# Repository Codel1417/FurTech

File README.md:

# FurTech

These are the files for a fursuit I am planning on making. I wanted eye displays for more expression, but then realized I cant see through the displays, Stereo cameras and an AR headset will be used for vision. The cameras will be hidden in the eyebrows. The jetson nano will handle stereo correction and managing the various sensors and servos. Once I have the hardware needed I will begin working on software. Base features are vision and ears reacting to sound. Then eye tracking using the cameras and opencv.

## Goals

* Eye Displays
* Ears which react to motion and environment
* Moving mouth to my voice
* Headpat detection and reactions
* Active cooling fan
* Stereo forward cameras
* AR/VR display for vision
* Eye Tracking (Vision or internal camera)
* No spaghetti 

## Hardware Features

Sensors connect over I2C

### Power Supply

* USB PD in @8-20V
* 3 5V 5A Linear Regulators
* Current Monitoring over I2C

### Sensors

* I2C Multiplexor
* Temperature Sensor
* 9-Axis IMU
* 5 Touch Sensors
* Cooling fan for comfort

### Ear Breakout

* Servo power switch
* i2C PWM Driver
* Mic/ADC input

### Display Driver

* 2 Display Connections
* Single output connection

### Jetson Nano Breakout

* I2C In
* Display SPI in
* Power in

## Other Hardware

* Nvidia Jetson Nano
* Nreal Air
* Stereo Cameras 1080P@60
* Usb PD battery
* 2x MatrixOrbital EVE3/4 displays
* 6x SG90 Servos

## 3D Printer STLs

* [https://www.thingiverse.com/thing:717901](https://www.thingiverse.com/thing:717901)

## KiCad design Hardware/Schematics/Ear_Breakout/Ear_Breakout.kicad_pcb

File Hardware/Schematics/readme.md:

The schematics were designed in [KiCad](https://www.kicad.org/) and use a consistent Resistor/Capacitor/LED size of 0603/1608 for ease of hand soldering. The AutoRouter plugin was used for data and low current traces. JST connectors are used to connect each board together.

Why split the boards? I was concerned about limited space inside the head so smaller boards let me contour the shape of the fursuit to reduce cable lengths and reduce the need to upscale the head. Smaller boards also allows for cheaper at con component swap out if something breaks.

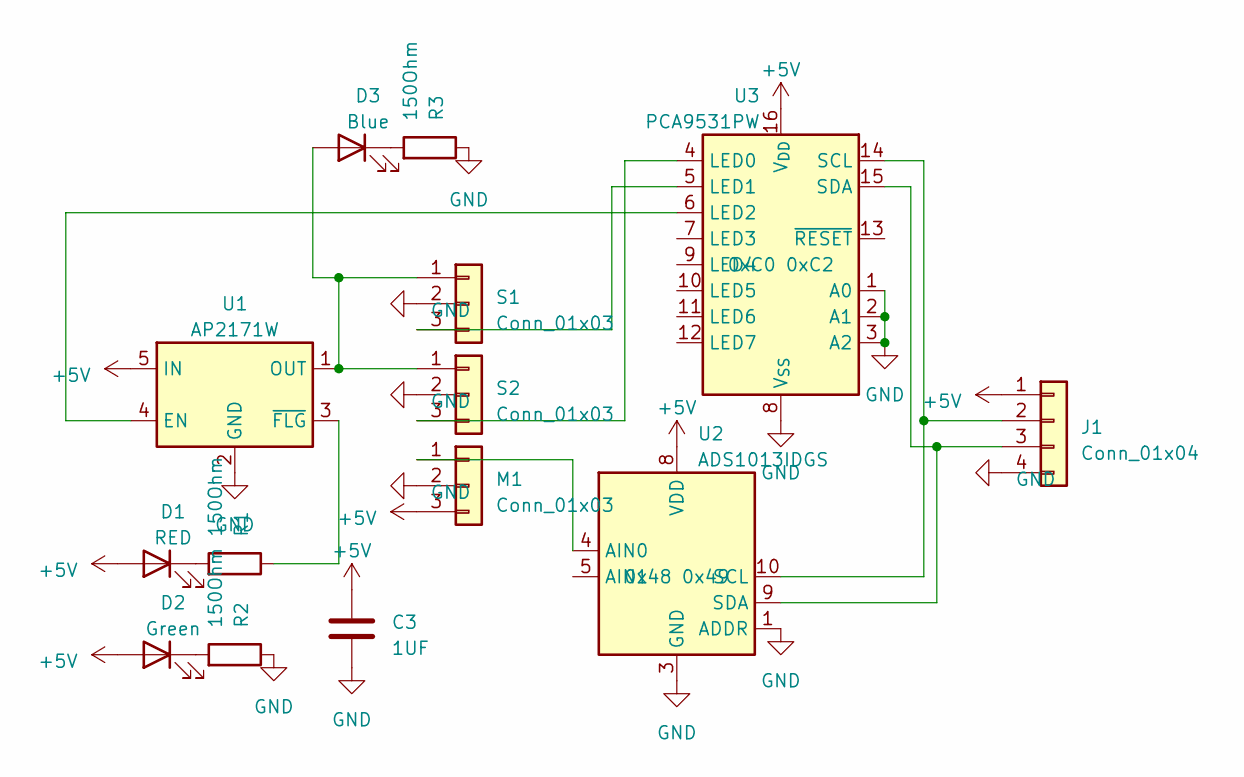
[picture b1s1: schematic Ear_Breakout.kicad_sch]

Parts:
C3: 1UF; C_0603_1608Metric_Pad1.08x0.95mm_HandSolder
D1: RED; LED_0603_1608Metric_Pad1.05x0.95mm_HandSolder
D2: Green; LED_0603_1608Metric_Pad1.05x0.95mm_HandSolder
D3: Blue; LED_0603_1608Metric_Pad1.05x0.95mm_HandSolder
J1: Conn_01x04; JST_EH_S4B-EH_1x04_P2.50mm_Horizontal
M1: Conn_01x03; PinHeader_1x03_P2.54mm_Horizontal
R1, R2, R3: 150Ohm; R_0603_1608Metric_Pad0.98x0.95mm_HandSolder
S1, S2: Conn_01x03; PinHeader_1x03_P2.54mm_Horizontal
U1: AP2171W; SOT-23-5
U2: ADS1013IDGS; TSSOP-10_3x3mm_P0.5mm
U3: PCA9531PW; TSSOP-16_4.4x5mm_P0.65mm

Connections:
+5V: C3.1, D1.2 (A), D2.2 (A), J1.1, M1.3, U1.5 (IN), U2.8 (VDD), U3.16 (V_{DD})
GND: C3.2, J1.4, M1.2, R2.1, R3.1, S1.2, S2.2, U1.2 (GND), U2.1 (ADDR), U2.3 (GND), U3.1 (A0), U3.2 (A1), U3.3 (A2), U3.8 (V_{SS})
unnamed: D1.1 (K), R1.2
unnamed: D2.1 (K), R2.2
unnamed: D3.2 (A), S1.1, S2.1, U1.1 (OUT)
unnamed: D3.1 (K), R3.2
unnamed: J1.2, U2.10 (SCL), U3.14 (SCL)
unnamed: J1.3, U2.9 (SDA), U3.15 (SDA)
unnamed: M1.1, U2.4 (AIN0)
unnamed: S1.3, U3.5 (LED1)
unnamed: S2.3, U3.4 (LED0)
unnamed: U1.4 (EN), U3.6 (LED2)
unnamed: R1.1, U1.3 (~FLG)

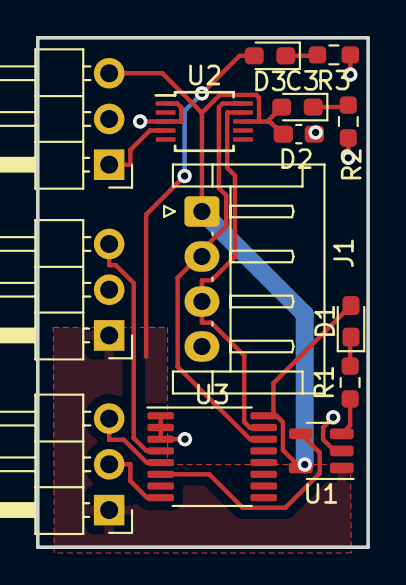
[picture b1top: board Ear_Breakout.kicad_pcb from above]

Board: 2 copper layers, 18.3 x 28.3 mm, 14 parts (0 on the bottom side), 13 nets.

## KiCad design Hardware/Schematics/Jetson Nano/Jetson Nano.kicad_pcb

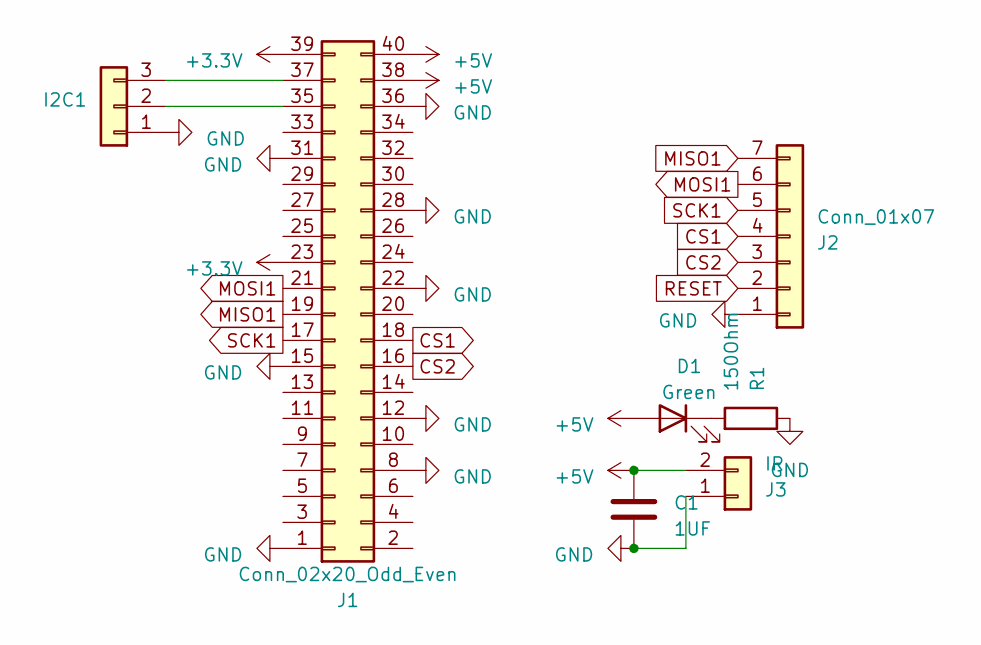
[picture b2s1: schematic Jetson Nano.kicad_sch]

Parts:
C1: 1UF; C_0603_1608Metric_Pad1.08x0.95mm_HandSolder
D1: Green; LED_0603_1608Metric_Pad1.05x0.95mm_HandSolder
I2C1: Conn_01x04; JST_EH_S3B-EH_1x03_P2.50mm_Horizontal
J1: Conn_02x20_Odd_Even; PinSocket_2x20_P2.54mm_Vertical
J2: Conn_01x07; JST_EH_S7B-EH_1x07_P2.50mm_Horizontal
J3: IR; JST_EH_S2B-EH_1x02_P2.50mm_Horizontal
R1: 150Ohm; R_0603_1608Metric_Pad0.98x0.95mm_HandSolder

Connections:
+3.3V: J1.23, J1.39
+5V: C1.1, D1.2 (A), J1.38, J1.40, J3.2
CS1: J1.18, J2.4
CS2: J1.16, J2.3
GND: C1.2, I2C1.1, J1.1, J1.8, J1.12, J1.15, J1.22, J1.28, J1.31, J1.36, J2.1, J3.1, R1.1
MISO1: J1.19, J2.7
MOSI1: J1.21, J2.6
unnamed: D1.1 (K), R1.2
unnamed: I2C1.2, J1.35
unnamed: I2C1.3, J1.37
RESET: J2.2
SCK1: J1.17, J2.5

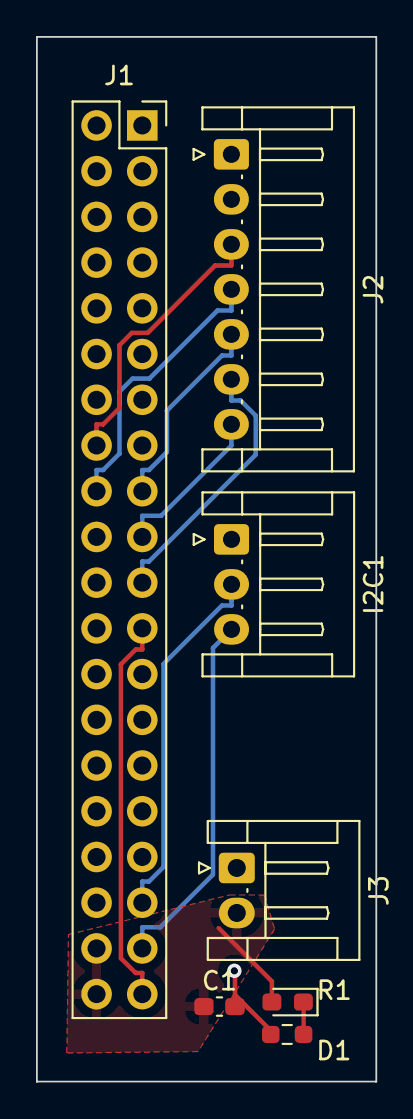
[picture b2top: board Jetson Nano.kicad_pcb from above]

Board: 2 copper layers, 18.9 x 58.0 mm, 7 parts (0 on the bottom side), 11 nets.

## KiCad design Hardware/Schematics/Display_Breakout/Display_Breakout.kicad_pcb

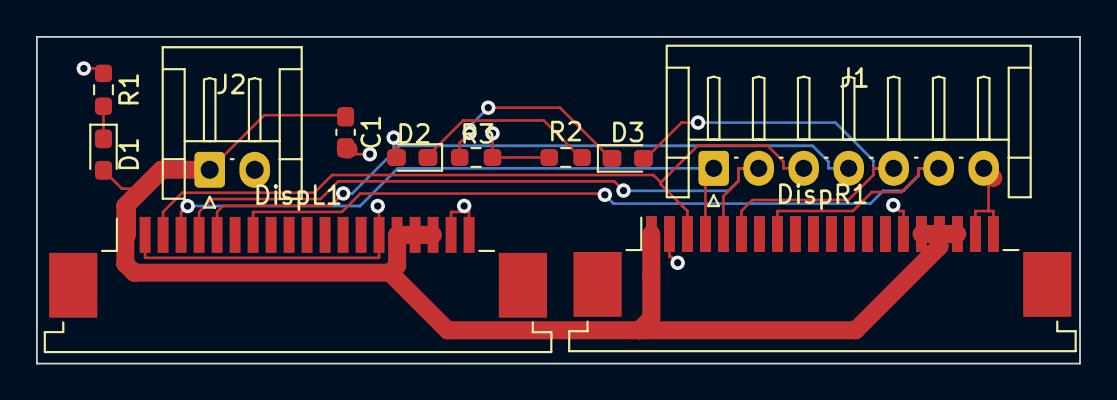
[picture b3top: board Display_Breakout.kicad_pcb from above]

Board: 2 copper layers, 57.9 x 18.1 mm, 11 parts (0 on the bottom side), 11 nets.

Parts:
C1: 4.7uf; C_0603_1608Metric_Pad1.08x0.95mm_HandSolder
D1: Green; LED_0603_1608Metric_Pad1.05x0.95mm_HandSolder
D2, D3: Blue; LED_0603_1608Metric_Pad1.05x0.95mm_HandSolder
DispL1: Conn_02x10_Odd_Even; TE_2-84952-0_1x20-1MP_P1.0mm_Horizontal
DispR1: Conn_02x10_Odd_Even; TE_2-84952-0_1x20-1MP_P1.0mm_Horizontal
J1: Conn_01x07; JST_EH_S7B-EH_1x07_P2.50mm_Horizontal
J2: Conn_01x02; JST_EH_S2B-EH_1x02_P2.50mm_Horizontal
R1, R2, R3: 150Ohm; R_0603_1608Metric_Pad0.98x0.95mm_HandSolder

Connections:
+5V: C1.1, D1.2 (A), DispL1.1, DispL1.16, DispL1.17, DispL1.18, DispR1.1, DispR1.16, DispR1.17, DispR1.18, J2.1
CS1: D2.2 (A), DispL1.6, J1.4
CS2: D3.2 (A), DispR1.6, J1.5
GND: C1.2, DispL1.2, DispL1.15, DispL1.19, DispL1.20, DispR1.2, DispR1.15, DispR1.19, DispR1.20, J1.7, J2.2, R1.1, R2.1, R3.1
MISO1: DispL1.4, DispR1.4, J1.1
MOSI1: DispL1.5, DispR1.5, J1.2
unnamed: D1.1 (K), R1.2
unnamed: D2.1 (K), R2.2
unnamed: D3.1 (K), R3.2
RESET: DispL1.8, DispR1.8, J1.6
SCK1: DispL1.3, DispR1.3, J1.3

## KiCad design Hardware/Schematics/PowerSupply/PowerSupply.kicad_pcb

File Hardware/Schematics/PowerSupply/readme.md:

The original design was for an external 18650 battery pack but due to safety concerns I switched to USB C and premade packs.

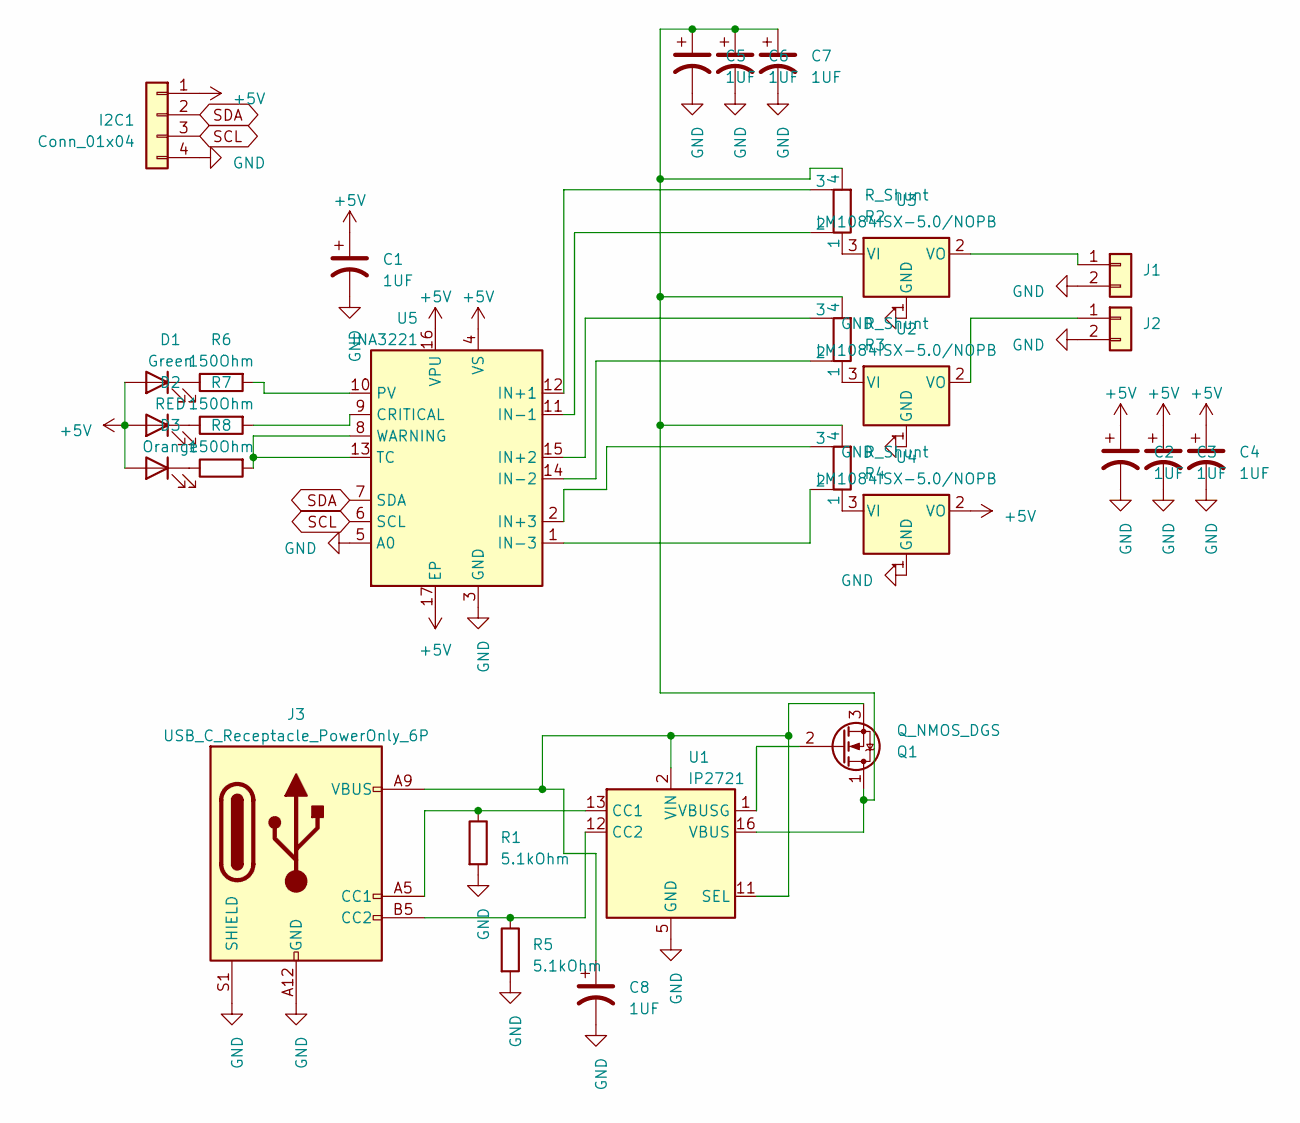
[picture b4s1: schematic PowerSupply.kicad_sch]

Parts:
C1, C2, C3, C4, C5, C6, C7, C8: 1UF; C_0603_1608Metric_Pad1.08x0.95mm_HandSolder
D1: Green; LED_0603_1608Metric_Pad1.05x0.95mm_HandSolder
D2: RED; LED_0603_1608Metric_Pad1.05x0.95mm_HandSolder
D3: Orange; LED_0603_1608Metric_Pad1.05x0.95mm_HandSolder
I2C1: Conn_01x04; JST_EH_S4B-EH_1x04_P2.50mm_Horizontal
J1, J2: JST_EH_S2B-EH_1x02_P2.50mm_Horizontal
J3: USB_C_Receptacle_PowerOnly_6P; USB_C_Receptacle_GCT_USB4135-GF-A_6P_TopMnt_Horizontal
Q1: Q_NMOS_DGS; TO-252-3_TabPin2
R1, R5: 5.1kOhm; R_0603_1608Metric
R2, R3, R4: R_Shunt; R_Shunt_Ohmite_LVK12
R6, R7, R8: 150Ohm; R_0603_1608Metric
U1: IP2721; TSSOP-16_4.4x5mm_P0.65mm
U2, U3, U4: LM1084ISX-5.0/NOPB; TO-263-3_TabPin2
U5: INA3221; Texas_RGV_S-PVQFN-N16_EP2.1x2.1mm

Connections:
+5V: C1.1, C2.1, C3.1, C4.1, D1.2 (A), D2.2 (A), D3.2 (A), I2C1.1, U4.2 (VO), U5.4 (VS), U5.16 (VPU), U5.17 (EP)
GND: C1.2, C2.2, C3.2, C4.2, C5.2, C6.2, C7.2, C8.2, I2C1.4, J1.2, J2.2, J3.A12 (GND), J3.B12 (GND), J3.S1 (SHIELD), R1.2, R5.2, U1.5 (GND), U2.1 (GND), U3.1 (GND), U4.1 (GND), U5.3 (GND), U5.5 (A0)
unnamed: D1.1 (K), R6.1
unnamed: D2.1 (K), R7.1
unnamed: D3.1 (K), R8.1
unnamed: J1.1, U3.2 (VO)
unnamed: J2.1, U2.2 (VO)
unnamed: J3.A5 (CC1), R1.1, U1.13 (CC1)
unnamed: J3.B5 (CC2), R5.1, U1.12 (CC2)
unnamed: C5.1, C6.1, C7.1, Q1.1 (D), R2.4, R3.4, R4.4, U1.16 (VBUS)
unnamed: Q1.2 (G), U1.1 (VBUSG)
unnamed: C8.1, J3.A9 (VBUS), J3.B9 (VBUS), Q1.3 (S), U1.2 (VIN), U1.11 (SEL)
unnamed: R3.1, U2.3 (VI)
unnamed: R2.1, U3.3 (VI)
unnamed: R4.1, U4.3 (VI)
unnamed: R7.2, U5.9 (CRITICAL)
unnamed: R2.3, U5.12 (IN+1)
unnamed: R3.3, U5.15 (IN+2)
unnamed: R4.3, U5.2 (IN+3)
unnamed: R2.2, U5.11 (IN-1)
unnamed: R3.2, U5.14 (IN-2)
unnamed: R4.2, U5.1 (IN-3)
unnamed: R6.2, U5.10 (PV)
unnamed: R8.2, U5.8 (WARNING), U5.13 (TC)
SCL: I2C1.3, U5.6 (SCL)
SDA: I2C1.2, U5.7 (SDA)

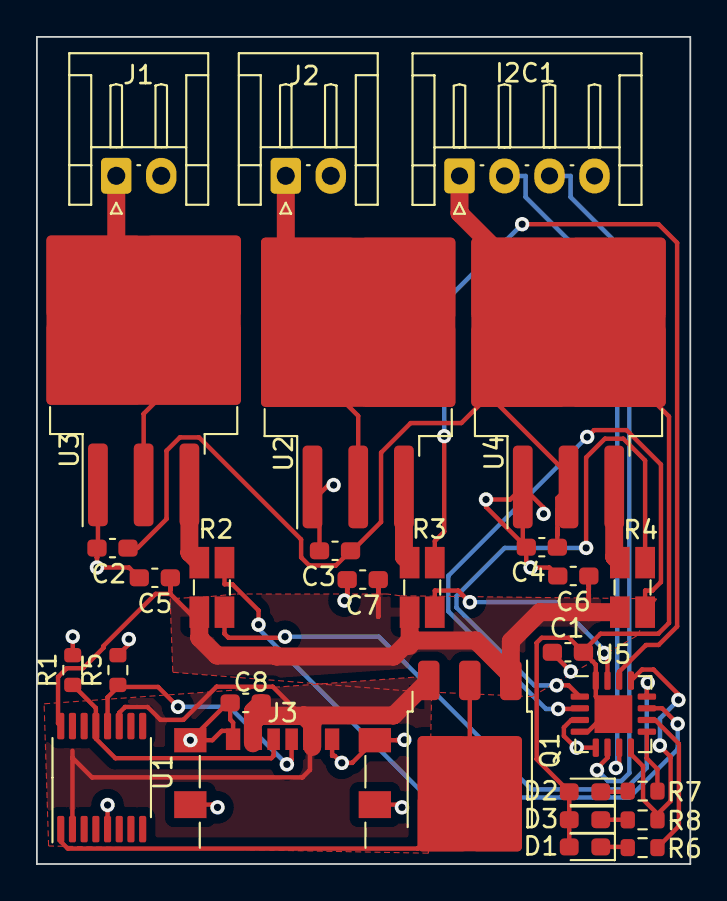
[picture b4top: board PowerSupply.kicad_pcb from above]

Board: 2 copper layers, 36.3 x 46.0 mm, 29 parts (0 on the bottom side), 26 nets.

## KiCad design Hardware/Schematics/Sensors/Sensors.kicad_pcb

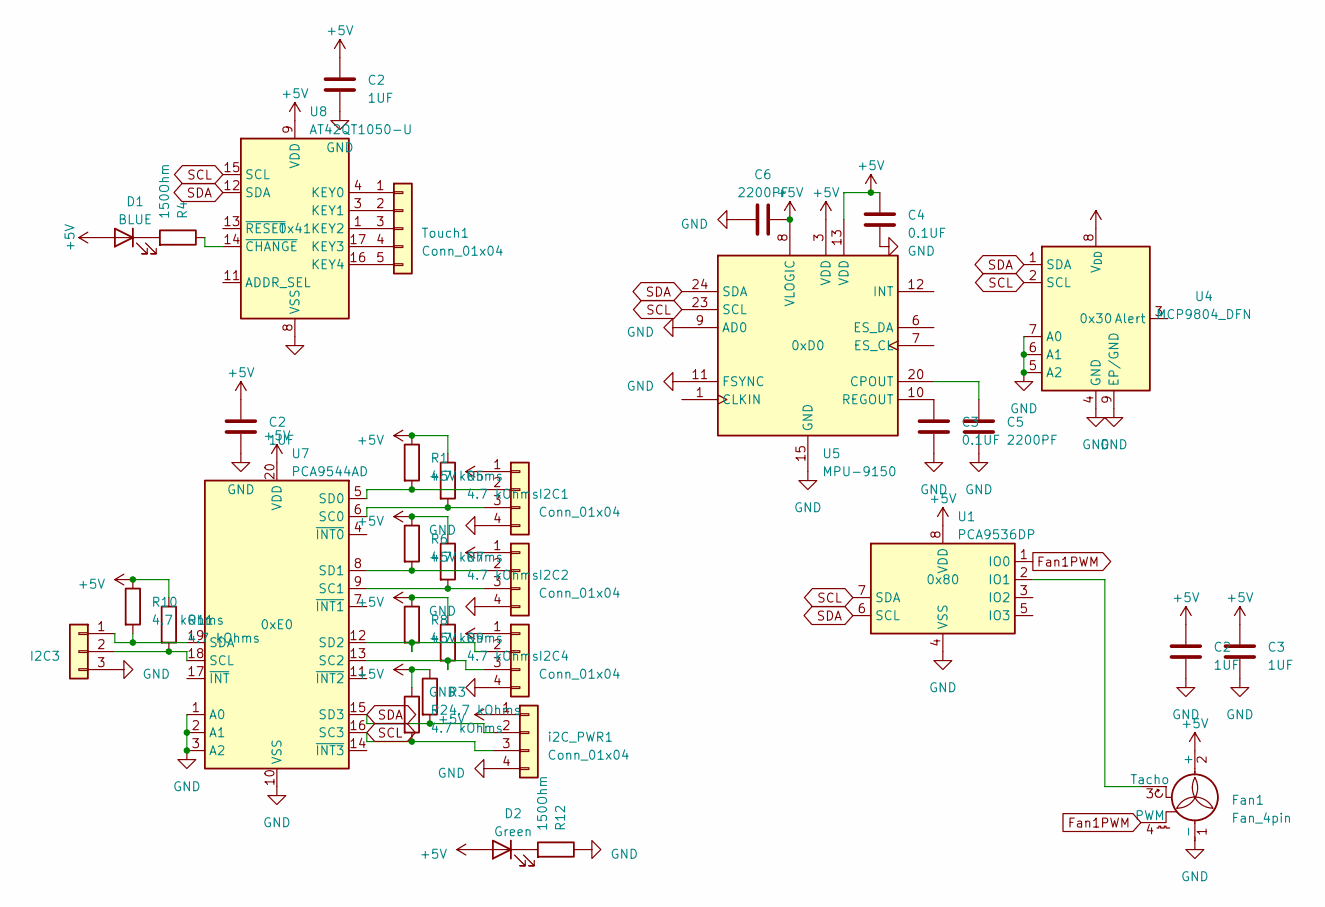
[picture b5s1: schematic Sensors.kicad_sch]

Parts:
C2: 1UF; C_0603_1608Metric_Pad1.08x0.95mm_HandSolder
C3, C4: 0.1UF; C_0603_1608Metric_Pad1.08x0.95mm_HandSolder
C5, C6: 2200PF; C_0603_1608Metric_Pad1.08x0.95mm_HandSolder
D1: BLUE; LED_0603_1608Metric_Pad1.05x0.95mm_HandSolder
D2: Green; LED_0603_1608Metric_Pad1.05x0.95mm_HandSolder
Fan1: Fan_4pin; FanPinHeader_1x04_P2.54mm_Vertical
I2C1, I2C2, I2C4: Conn_01x04; JST_EH_S4B-EH_1x04_P2.50mm_Horizontal
I2C3: Conn_01x03; JST_EH_S3B-EH_1x03_P2.50mm_Horizontal
R1, R2, R3, R5, R6, R7, R8, R9, R10, R11: 4.7 kOhms; R_0603_1608Metric
R4, R12: 150Ohm; R_0603_1608Metric_Pad0.98x0.95mm_HandSolder
Touch1: Conn_01x04; PinHeader_1x05_P2.54mm_Horizontal
U1: PCA9536DP; TSSOP-8_3x3mm_P0.65mm
U4: MCP9804_DFN; DFN-8-1EP_3x2mm_P0.5mm_EP1.7x1.4mm
U5: MPU-9150; InvenSense_QFN-24_4x4mm_P0.5mm
U7: PCA9544AD; TSSOP-20_4.4x6.5mm_P0.65mm
U8: AT42QT1050-U; VQFN-20-1EP_3x3mm_P0.45mm_EP1.55x1.55mm
i2C_PWR1: Conn_01x04; JST_EH_S4B-EH_1x04_P2.50mm_Horizontal

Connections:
Fan1PWM: Fan1.4 (PWM), U1.1 (IO0)
GND: C2.2, C3.2, C4.2, C5.2, C6.2, Fan1.1 (-), I2C1.4, I2C2.4, I2C3.3, I2C4.4, R12.1, U1.4 (VSS), U4.4 (GND), U4.5 (A2), U4.6 (A1), U4.7 (A0), U4.9 (EP/GND), U5.9 (AD0), U5.11 (FSYNC), U5.15 (GND), U5.17 (GND), U5.18 (GND), U7.1 (A0), U7.2 (A1), U7.3 (A2), U7.10 (VSS), U8.8 (VSS), U8.21 (VSS), i2C_PWR1.4; also elsewhere on the board
unnamed: D1.1 (K), R4.2
unnamed: D2.1 (K), R12.2
unnamed: Fan1.3 (Tacho), U1.2 (IO1)
unnamed: I2C1.2, R1.2, U7.5 (SD0)
unnamed: I2C1.3, R5.2, U7.6 (SC0)
unnamed: I2C2.2, R6.2, U7.8 (SD1)
unnamed: I2C2.3, R7.2, U7.9 (SC1)
unnamed: I2C3.1, R10.2, U7.19 (SDA)
unnamed: I2C3.2, R11.2, U7.18 (SCL)
unnamed: I2C4.2, R8.2, U7.12 (SD2)
unnamed: I2C4.3, R9.2, U7.13 (SC2)
unnamed: Touch1.1, U8.4 (KEY0)
unnamed: Touch1.2, U8.3 (KEY1)
unnamed: Touch1.3, U8.1 (KEY2)
unnamed: Touch1.4, U8.17 (KEY3)
unnamed: Touch1.5, U8.16 (KEY4)
unnamed: C5.1, U5.20 (CPOUT)
unnamed: R4.1, U8.14 (~CHANGE)
SCL: R2.2, U1.7 (SDA), U4.2 (SCL), U5.23 (SCL), U7.16 (SC3), U8.15 (SCL), i2C_PWR1.3
SDA: R3.2, U1.6 (SCL), U4.1 (SDA), U5.24 (SDA), U7.15 (SD3), U8.12 (SDA), i2C_PWR1.2

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
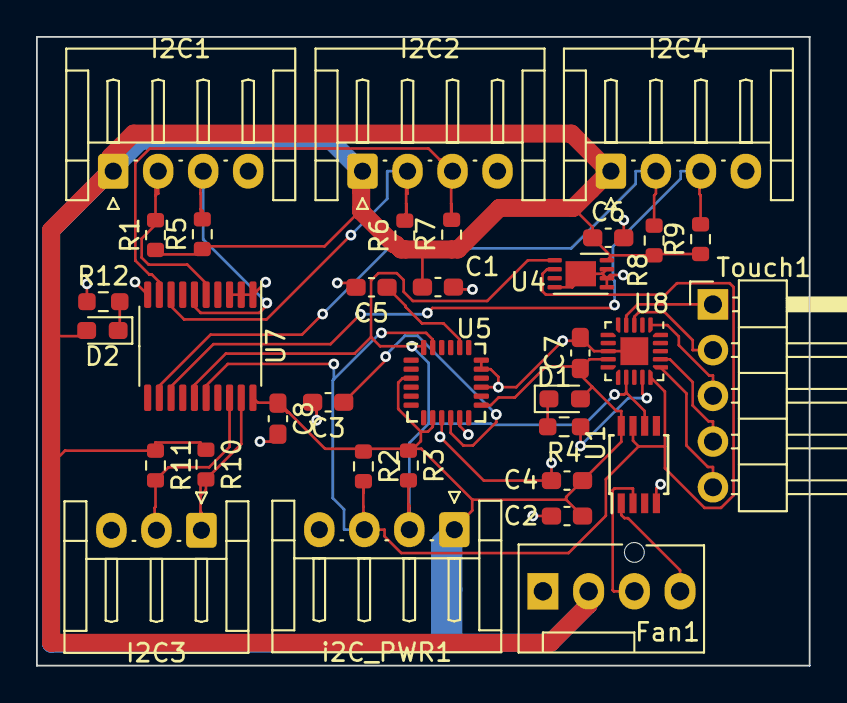
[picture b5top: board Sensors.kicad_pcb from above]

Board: 2 copper layers, 42.9 x 34.9 mm, 34 parts (0 on the bottom side), 24 nets.

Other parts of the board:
C1, C7, C8: 1UF; C_0603_1608Metric_Pad1.08x0.95mm_HandSolder

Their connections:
GND: C1.2, C7.2, C8.2; also elsewhere on the board

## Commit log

2023-04-05 V1 Hardware schematics
